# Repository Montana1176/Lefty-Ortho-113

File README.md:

# Lefty-Ortho-113
113 Key Ortholinear Keyboard with Left Num Pad

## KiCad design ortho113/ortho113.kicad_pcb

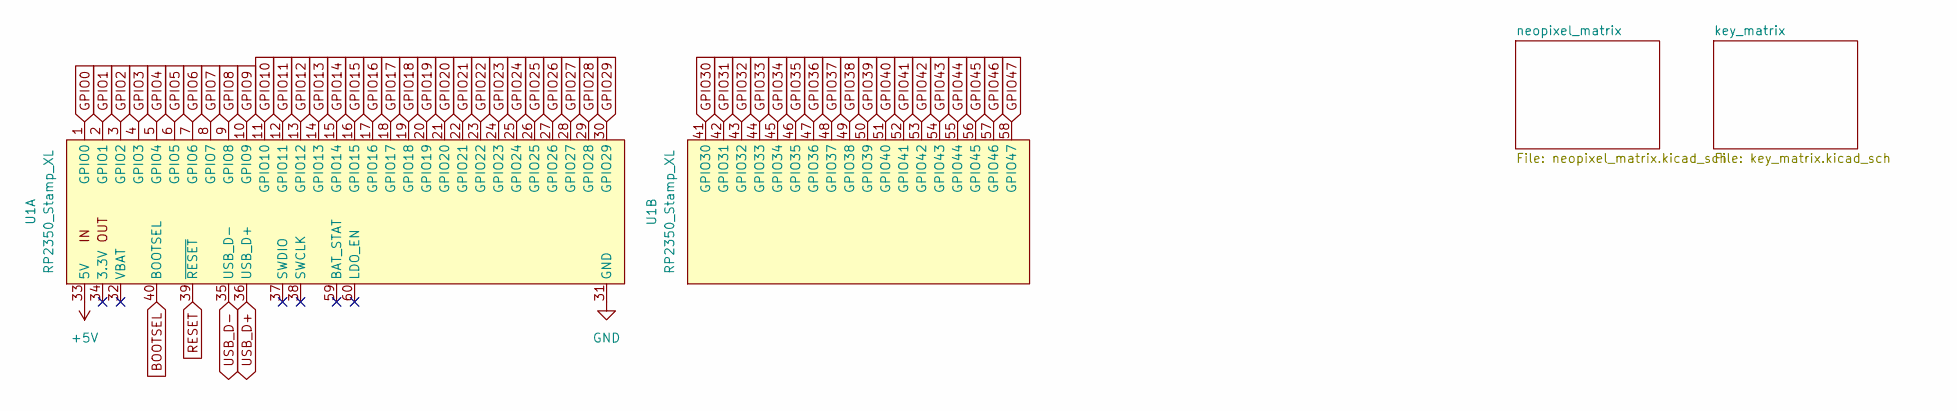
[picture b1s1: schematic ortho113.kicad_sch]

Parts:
U1: RP2350_Stamp_XL; RP2xxx_Stamp_XL_THT

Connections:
+5V: U1.33 (5V); also elsewhere on the board
BOOTSEL: U1.40 (BOOTSEL)
GND: U1.31 (GND); also elsewhere on the board
GPIO0: U1.1 (GPIO0)
GPIO1: U1.2 (GPIO1); also elsewhere on the board
GPIO2: U1.3 (GPIO2)
GPIO3: U1.4 (GPIO3)
GPIO4: U1.5 (GPIO4)
GPIO5: U1.6 (GPIO5)
GPIO6: U1.7 (GPIO6)
GPIO7: U1.8 (GPIO7)
GPIO8: U1.9 (GPIO8)
GPIO9: U1.10 (GPIO9)
GPIO10: U1.11 (GPIO10)
GPIO11: U1.12 (GPIO11)
GPIO12: U1.13 (GPIO12)
GPIO13: U1.14 (GPIO13)
GPIO14: U1.15 (GPIO14)
GPIO15: U1.16 (GPIO15)
GPIO16: U1.17 (GPIO16)
GPIO17: U1.18 (GPIO17)
GPIO18: U1.19 (GPIO18)
GPIO19: U1.20 (GPIO19)
GPIO20: U1.21 (GPIO20)
GPIO21: U1.22 (GPIO21)
GPIO22: U1.23 (GPIO22)
GPIO23: U1.24 (GPIO23)
GPIO24: U1.25 (GPIO24)
GPIO25: U1.26 (GPIO25)
GPIO26: U1.27 (GPIO26)
GPIO27: U1.28 (GPIO27)
GPIO28: U1.29 (GPIO28)
GPIO29: U1.30 (GPIO29)
GPIO30: U1.41 (GPIO30)
GPIO31: U1.42 (GPIO31)
GPIO32: U1.43 (GPIO32)
GPIO33: U1.44 (GPIO33)
GPIO34: U1.45 (GPIO34)
GPIO35: U1.46 (GPIO35)
GPIO36: U1.47 (GPIO36)
GPIO37: U1.48 (GPIO37)
GPIO38: U1.49 (GPIO38)
GPIO39: U1.50 (GPIO39)
GPIO40: U1.51 (GPIO40)
GPIO41: U1.52 (GPIO41)
GPIO42: U1.53 (GPIO42)
GPIO43: U1.54 (GPIO43)
GPIO44: U1.55 (GPIO44)
GPIO45: U1.56 (GPIO45)
GPIO46: U1.57 (GPIO46)
GPIO47: U1.58 (GPIO47)
RESET: U1.39 (~RESET)
USB_D+: U1.36 (USB_D+)
USB_D-: U1.35 (USB_D-)

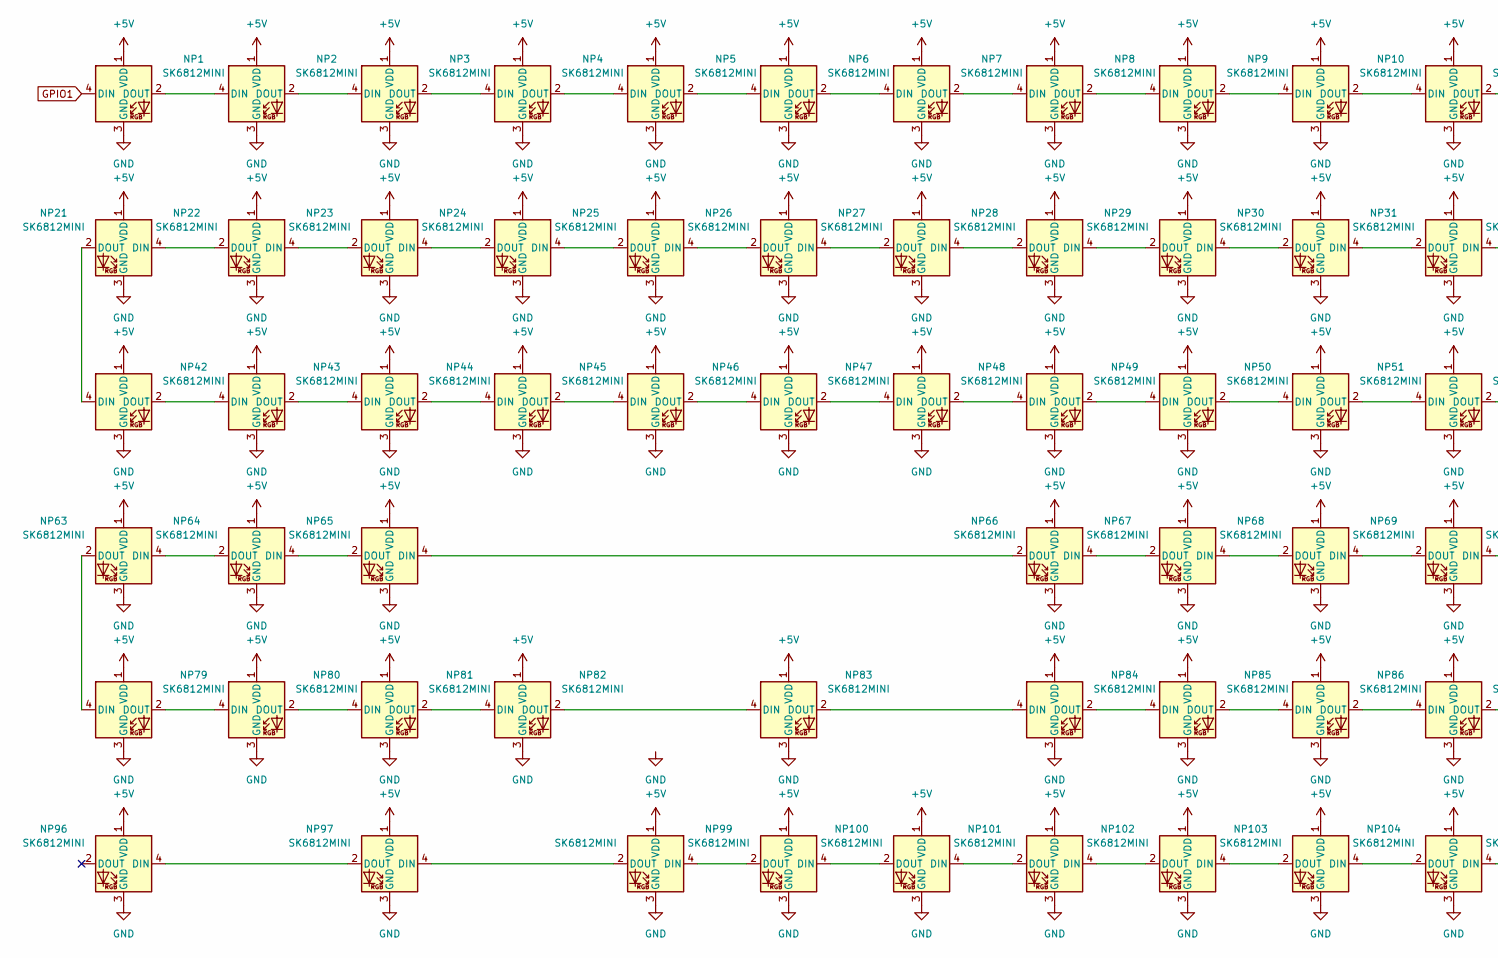
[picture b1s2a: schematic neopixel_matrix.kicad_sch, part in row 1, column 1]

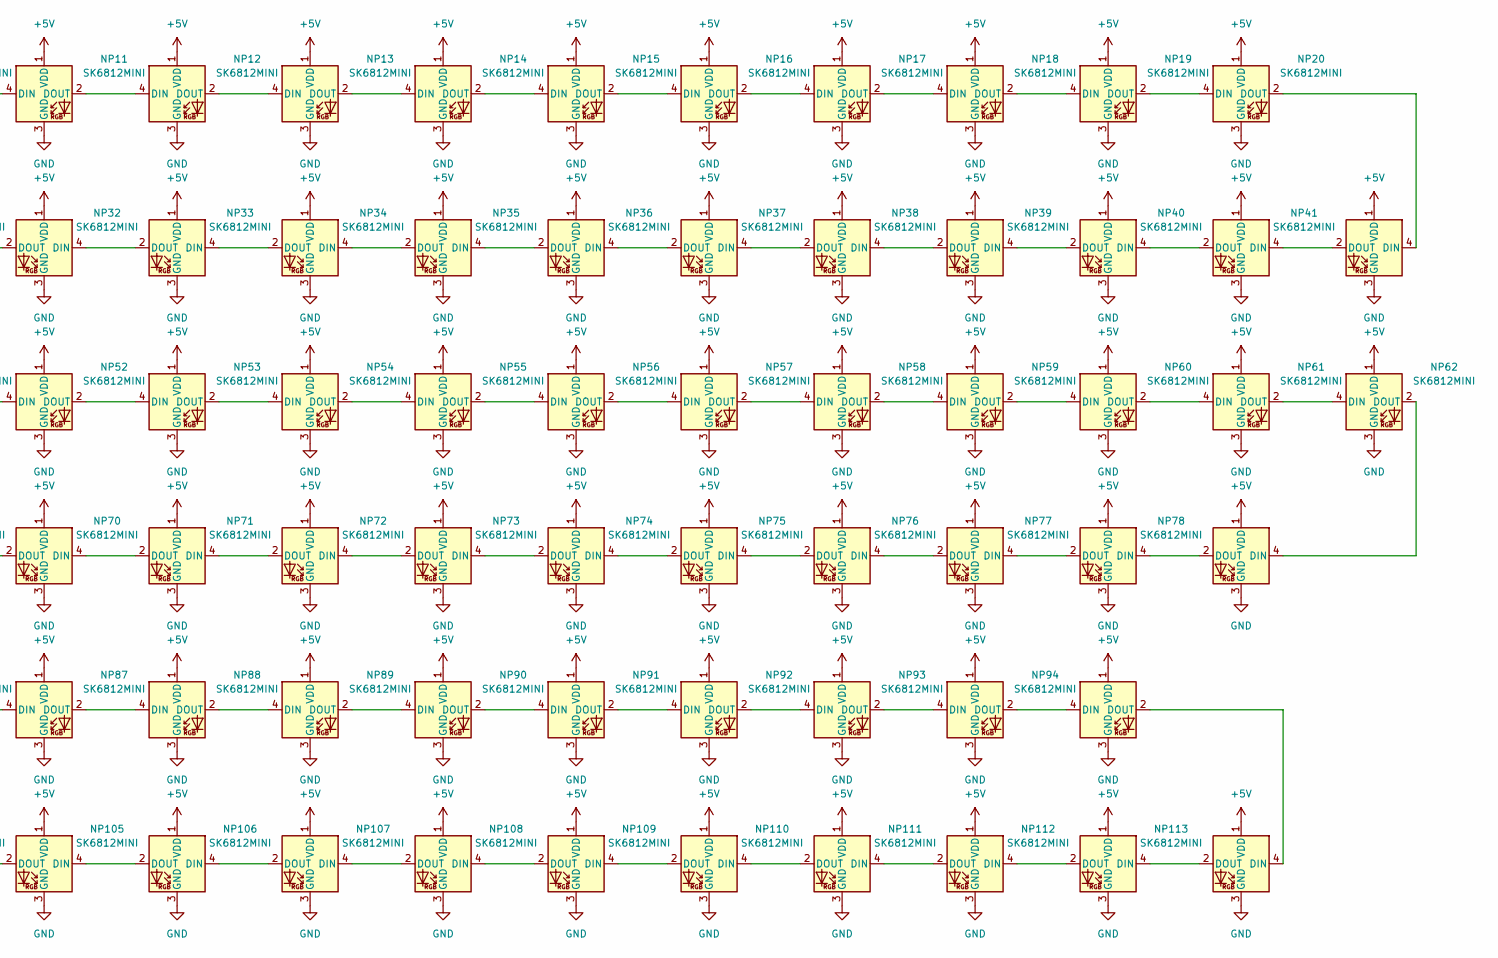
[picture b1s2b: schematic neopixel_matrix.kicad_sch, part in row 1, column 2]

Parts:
NP1, NP2, NP3, NP4, NP5, NP6, NP7, NP8, NP9, NP10, NP11, NP12, NP13, NP14, NP15, NP16, NP17, NP18, NP19, NP20, NP21, NP22, NP23, NP24, NP25, NP26, NP27, NP28, NP29, NP30, NP31, NP32, NP33, NP34, NP35, NP36, NP37, NP38, NP39, NP40, NP41, NP42, NP43, NP44, NP45, NP46, NP47, NP48, NP49, NP50, NP51, NP52, NP53, NP54, NP55, NP56, NP57, NP58, NP59, NP60, NP61, NP62, NP63, NP64, NP65, NP66, NP67, NP68, NP69, NP70, NP71, NP72, NP73, NP74, NP75, NP76, NP77, NP78, NP79, NP80, NP81, NP82, NP83, NP84, NP85, NP86, NP87, NP88, NP89, NP90, NP91, NP92, NP93, NP94, NP95, NP96, NP97, NP98, NP99, NP100, NP101, NP102, NP103, NP104, NP105, NP106, NP107, NP109, NP110, NP111, NP112, NP113: SK6812MINI; LED_SK6812MINI_PLCC4_3.5x3.5mm_P1.75mm
NP108: SK6812MINI; LED_SK6812MINI_E

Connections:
+5V: NP1.1 (VDD), NP2.1 (VDD), NP3.1 (VDD), NP4.1 (VDD), NP5.1 (VDD), NP6.1 (VDD), NP7.1 (VDD), NP8.1 (VDD), NP9.1 (VDD), NP10.1 (VDD), NP11.1 (VDD), NP12.1 (VDD), NP13.1 (VDD), NP14.1 (VDD), NP15.1 (VDD), NP16.1 (VDD), NP17.1 (VDD), NP18.1 (VDD), NP19.1 (VDD), NP20.1 (VDD), NP21.1 (VDD), NP22.1 (VDD), NP23.1 (VDD), NP24.1 (VDD), NP25.1 (VDD), NP26.1 (VDD), NP27.1 (VDD), NP28.1 (VDD), NP29.1 (VDD), NP30.1 (VDD), NP31.1 (VDD), NP32.1 (VDD), NP33.1 (VDD), NP34.1 (VDD), NP35.1 (VDD), NP36.1 (VDD), NP37.1 (VDD), NP38.1 (VDD), NP39.1 (VDD), NP40.1 (VDD), NP41.1 (VDD), NP42.1 (VDD), NP43.1 (VDD), NP44.1 (VDD), NP45.1 (VDD), NP46.1 (VDD), NP47.1 (VDD), NP48.1 (VDD), NP49.1 (VDD), NP50.1 (VDD), NP51.1 (VDD), NP52.1 (VDD), NP53.1 (VDD), NP54.1 (VDD), NP55.1 (VDD), NP56.1 (VDD), NP57.1 (VDD), NP58.1 (VDD), NP59.1 (VDD), NP60.1 (VDD), NP61.1 (VDD), NP62.1 (VDD), NP63.1 (VDD), NP64.1 (VDD), NP65.1 (VDD), NP66.1 (VDD), NP67.1 (VDD), NP68.1 (VDD), NP69.1 (VDD), NP70.1 (VDD), NP71.1 (VDD), NP72.1 (VDD), NP73.1 (VDD), NP74.1 (VDD), NP75.1 (VDD), NP76.1 (VDD), NP77.1 (VDD), NP78.1 (VDD), NP79.1 (VDD), NP80.1 (VDD), NP81.1 (VDD), NP82.1 (VDD), NP83.1 (VDD), NP84.1 (VDD), NP85.1 (VDD), NP86.1 (VDD), NP87.1 (VDD), NP88.1 (VDD), NP89.1 (VDD), NP90.1 (VDD), NP91.1 (VDD), NP92.1 (VDD), NP93.1 (VDD), NP94.1 (VDD), NP95.1 (VDD), NP96.1 (VDD), NP97.1 (VDD), NP98.1 (VDD), NP99.1 (VDD), NP100.1 (VDD), NP101.1 (VDD), NP102.1 (VDD), NP103.1 (VDD), NP104.1 (VDD), NP105.1 (VDD), NP106.1 (VDD), NP107.1 (VDD), NP108.1 (VDD), NP109.1 (VDD), NP110.1 (VDD), NP111.1 (VDD), NP112.1 (VDD), NP113.1 (VDD); also elsewhere on the board
GND: NP1.3 (GND), NP2.3 (GND), NP3.3 (GND), NP4.3 (GND), NP5.3 (GND), NP6.3 (GND), NP7.3 (GND), NP8.3 (GND), NP9.3 (GND), NP10.3 (GND), NP11.3 (GND), NP12.3 (GND), NP13.3 (GND), NP14.3 (GND), NP15.3 (GND), NP16.3 (GND), NP17.3 (GND), NP18.3 (GND), NP19.3 (GND), NP20.3 (GND), NP21.3 (GND), NP22.3 (GND), NP23.3 (GND), NP24.3 (GND), NP25.3 (GND), NP26.3 (GND), NP27.3 (GND), NP28.3 (GND), NP29.3 (GND), NP30.3 (GND), NP31.3 (GND), NP32.3 (GND), NP33.3 (GND), NP34.3 (GND), NP35.3 (GND), NP36.3 (GND), NP37.3 (GND), NP38.3 (GND), NP39.3 (GND), NP40.3 (GND), NP41.3 (GND), NP42.3 (GND), NP43.3 (GND), NP44.3 (GND), NP45.3 (GND), NP46.3 (GND), NP47.3 (GND), NP48.3 (GND), NP49.3 (GND), NP50.3 (GND), NP51.3 (GND), NP52.3 (GND), NP53.3 (GND), NP54.3 (GND), NP55.3 (GND), NP56.3 (GND), NP57.3 (GND), NP58.3 (GND), NP59.3 (GND), NP60.3 (GND), NP61.3 (GND), NP62.3 (GND), NP63.3 (GND), NP64.3 (GND), NP65.3 (GND), NP66.3 (GND), NP67.3 (GND), NP68.3 (GND), NP69.3 (GND), NP70.3 (GND), NP71.3 (GND), NP72.3 (GND), NP73.3 (GND), NP74.3 (GND), NP75.3 (GND), NP76.3 (GND), NP77.3 (GND), NP78.3 (GND), NP79.3 (GND), NP80.3 (GND), NP81.3 (GND), NP82.3 (GND), NP83.3 (GND), NP84.3 (GND), NP85.3 (GND), NP86.3 (GND), NP87.3 (GND), NP88.3 (GND), NP89.3 (GND), NP90.3 (GND), NP91.3 (GND), NP92.3 (GND), NP93.3 (GND), NP94.3 (GND), NP95.3 (GND), NP96.3 (GND), NP97.3 (GND), NP98.3 (GND), NP99.3 (GND), NP100.3 (GND), NP101.3 (GND), NP102.3 (GND), NP103.3 (GND), NP104.3 (GND), NP105.3 (GND), NP106.3 (GND), NP107.3 (GND), NP108.3 (GND), NP109.3 (GND), NP110.3 (GND), NP111.3 (GND), NP112.3 (GND), NP113.3 (GND); also elsewhere on the board
GPIO1: NP1.4 (DIN); also elsewhere on the board
unnamed: NP1.2 (DOUT), NP2.4 (DIN)
unnamed: NP2.2 (DOUT), NP3.4 (DIN)
unnamed: NP3.2 (DOUT), NP4.4 (DIN)
unnamed: NP4.2 (DOUT), NP5.4 (DIN)
unnamed: NP5.2 (DOUT), NP6.4 (DIN)
unnamed: NP6.2 (DOUT), NP7.4 (DIN)
unnamed: NP7.2 (DOUT), NP8.4 (DIN)
unnamed: NP8.2 (DOUT), NP9.4 (DIN)
unnamed: NP9.2 (DOUT), NP10.4 (DIN)
unnamed: NP10.2 (DOUT), NP11.4 (DIN)
unnamed: NP11.2 (DOUT), NP12.4 (DIN)
unnamed: NP12.2 (DOUT), NP13.4 (DIN)
unnamed: NP13.2 (DOUT), NP14.4 (DIN)
unnamed: NP14.2 (DOUT), NP15.4 (DIN)
unnamed: NP15.2 (DOUT), NP16.4 (DIN)
unnamed: NP16.2 (DOUT), NP17.4 (DIN)
unnamed: NP17.2 (DOUT), NP18.4 (DIN)
unnamed: NP18.2 (DOUT), NP19.4 (DIN)
unnamed: NP19.2 (DOUT), NP20.4 (DIN)
unnamed: NP20.2 (DOUT), NP41.4 (DIN)
unnamed: NP21.4 (DIN), NP22.2 (DOUT)
unnamed: NP21.2 (DOUT), NP42.4 (DIN)
unnamed: NP22.4 (DIN), NP23.2 (DOUT)
unnamed: NP23.4 (DIN), NP24.2 (DOUT)
unnamed: NP24.4 (DIN), NP25.2 (DOUT)
unnamed: NP25.4 (DIN), NP26.2 (DOUT)
unnamed: NP26.4 (DIN), NP27.2 (DOUT)
unnamed: NP27.4 (DIN), NP28.2 (DOUT)
unnamed: NP28.4 (DIN), NP29.2 (DOUT)
unnamed: NP29.4 (DIN), NP30.2 (DOUT)
unnamed: NP30.4 (DIN), NP31.2 (DOUT)
unnamed: NP31.4 (DIN), NP32.2 (DOUT)
unnamed: NP32.4 (DIN), NP33.2 (DOUT)
unnamed: NP33.4 (DIN), NP34.2 (DOUT)
unnamed: NP34.4 (DIN), NP35.2 (DOUT)
unnamed: NP35.4 (DIN), NP36.2 (DOUT)
unnamed: NP36.4 (DIN), NP37.2 (DOUT)
unnamed: NP37.4 (DIN), NP38.2 (DOUT)
unnamed: NP38.4 (DIN), NP39.2 (DOUT)
unnamed: NP39.4 (DIN), NP40.2 (DOUT)
unnamed: NP40.4 (DIN), NP41.2 (DOUT)
unnamed: NP42.2 (DOUT), NP43.4 (DIN)
unnamed: NP43.2 (DOUT), NP44.4 (DIN)
unnamed: NP44.2 (DOUT), NP45.4 (DIN)
unnamed: NP45.2 (DOUT), NP46.4 (DIN)
unnamed: NP46.2 (DOUT), NP47.4 (DIN)
unnamed: NP47.2 (DOUT), NP48.4 (DIN)
unnamed: NP48.2 (DOUT), NP49.4 (DIN)
unnamed: NP49.2 (DOUT), NP50.4 (DIN)
unnamed: NP50.2 (DOUT), NP51.4 (DIN)
unnamed: NP51.2 (DOUT), NP52.4 (DIN)
unnamed: NP52.2 (DOUT), NP53.4 (DIN)
unnamed: NP53.2 (DOUT), NP54.4 (DIN)
unnamed: NP54.2 (DOUT), NP55.4 (DIN)
unnamed: NP55.2 (DOUT), NP56.4 (DIN)
unnamed: NP56.2 (DOUT), NP57.4 (DIN)
unnamed: NP57.2 (DOUT), NP58.4 (DIN)
unnamed: NP58.2 (DOUT), NP59.4 (DIN)
unnamed: NP59.2 (DOUT), NP60.4 (DIN)
unnamed: NP60.2 (DOUT), NP61.4 (DIN)
unnamed: NP61.2 (DOUT), NP62.4 (DIN)
unnamed: NP62.2 (DOUT), NP78.4 (DIN)
unnamed: NP63.4 (DIN), NP64.2 (DOUT)
unnamed: NP63.2 (DOUT), NP79.4 (DIN)
unnamed: NP64.4 (DIN), NP65.2 (DOUT)
unnamed: NP65.4 (DIN), NP66.2 (DOUT)
unnamed: NP66.4 (DIN), NP67.2 (DOUT)
unnamed: NP67.4 (DIN), NP68.2 (DOUT)
unnamed: NP68.4 (DIN), NP69.2 (DOUT)
unnamed: NP69.4 (DIN), NP70.2 (DOUT)
unnamed: NP70.4 (DIN), NP71.2 (DOUT)
unnamed: NP71.4 (DIN), NP72.2 (DOUT)
unnamed: NP72.4 (DIN), NP73.2 (DOUT)
unnamed: NP73.4 (DIN), NP74.2 (DOUT)
unnamed: NP74.4 (DIN), NP75.2 (DOUT)
unnamed: NP75.4 (DIN), NP76.2 (DOUT)
unnamed: NP76.4 (DIN), NP77.2 (DOUT)
unnamed: NP77.4 (DIN), NP78.2 (DOUT)
unnamed: NP79.2 (DOUT), NP80.4 (DIN)
unnamed: NP80.2 (DOUT), NP81.4 (DIN)
unnamed: NP81.2 (DOUT), NP82.4 (DIN)
unnamed: NP82.2 (DOUT), NP83.4 (DIN)
unnamed: NP83.2 (DOUT), NP84.4 (DIN)
unnamed: NP84.2 (DOUT), NP85.4 (DIN)
unnamed: NP85.2 (DOUT), NP86.4 (DIN)
unnamed: NP86.2 (DOUT), NP87.4 (DIN)
unnamed: NP87.2 (DOUT), NP88.4 (DIN)
unnamed: NP88.2 (DOUT), NP89.4 (DIN)
unnamed: NP89.2 (DOUT), NP90.4 (DIN)
unnamed: NP90.2 (DOUT), NP91.4 (DIN)
unnamed: NP91.2 (DOUT), NP92.4 (DIN)
unnamed: NP92.2 (DOUT), NP93.4 (DIN)
unnamed: NP93.2 (DOUT), NP94.4 (DIN)
unnamed: NP94.2 (DOUT), NP95.4 (DIN)
unnamed: NP96.4 (DIN), NP97.2 (DOUT)
unnamed: NP97.4 (DIN), NP98.2 (DOUT)
unnamed: NP98.4 (DIN), NP99.2 (DOUT)
unnamed: NP100.4 (DIN), NP101.2 (DOUT)
unnamed: NP99.4 (DIN), NP100.2 (DOUT)
unnamed: NP101.4 (DIN), NP102.2 (DOUT)
unnamed: NP102.4 (DIN), NP103.2 (DOUT)
unnamed: NP103.4 (DIN), NP104.2 (DOUT)
unnamed: NP104.4 (DIN), NP105.2 (DOUT)
unnamed: NP105.4 (DIN), NP106.2 (DOUT)
unnamed: NP106.4 (DIN), NP107.2 (DOUT)
unnamed: NP107.4 (DIN), NP108.2 (DOUT)
unnamed: NP108.4 (DIN), NP109.2 (DOUT)
unnamed: NP109.4 (DIN), NP110.2 (DOUT)
unnamed: NP110.4 (DIN), NP111.2 (DOUT)
unnamed: NP111.4 (DIN), NP112.2 (DOUT)
unnamed: NP112.4 (DIN), NP113.2 (DOUT)
unnamed: NP95.2 (DOUT), NP113.4 (DIN)

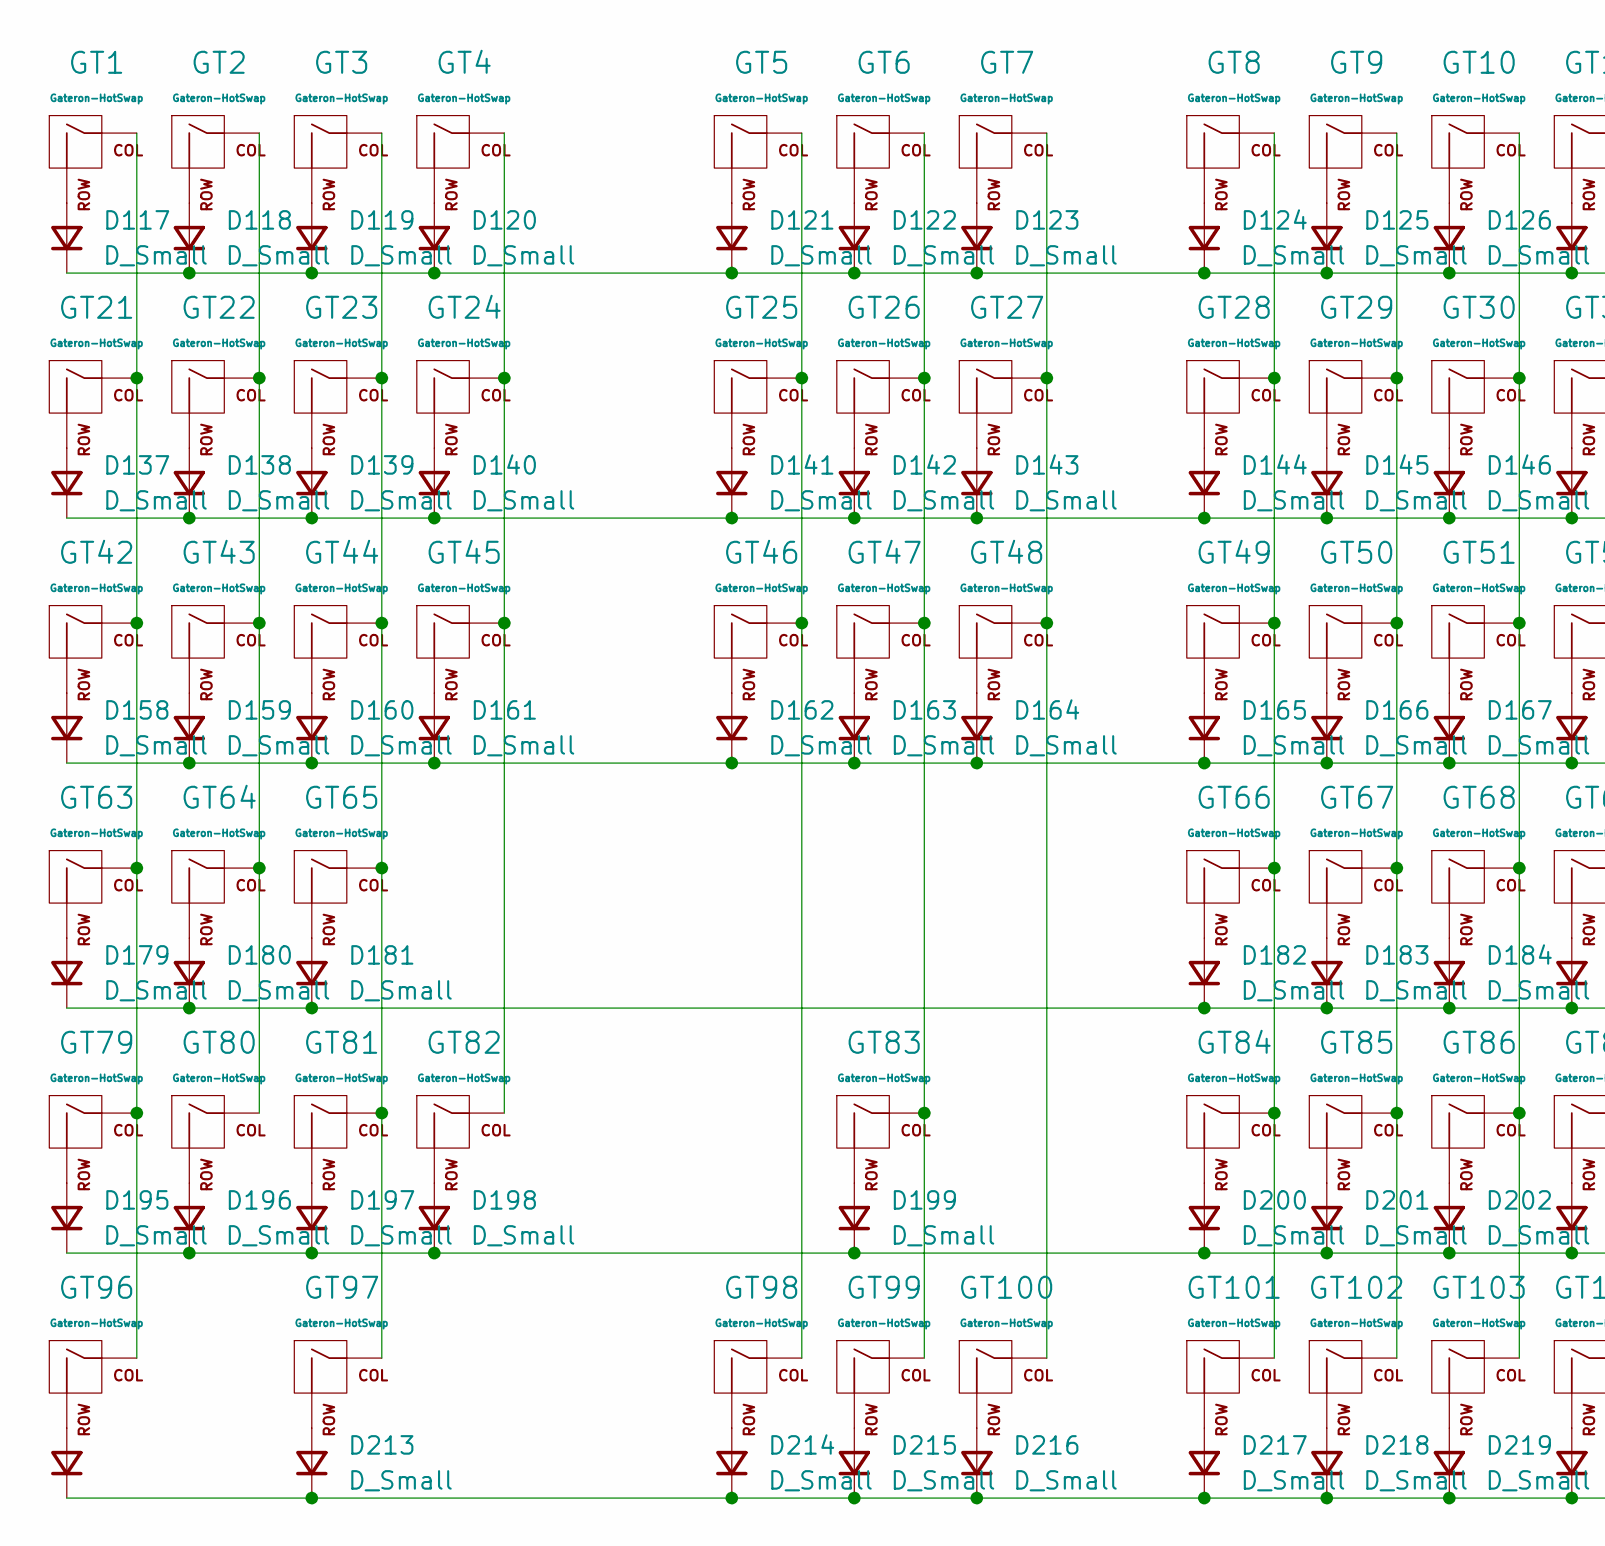
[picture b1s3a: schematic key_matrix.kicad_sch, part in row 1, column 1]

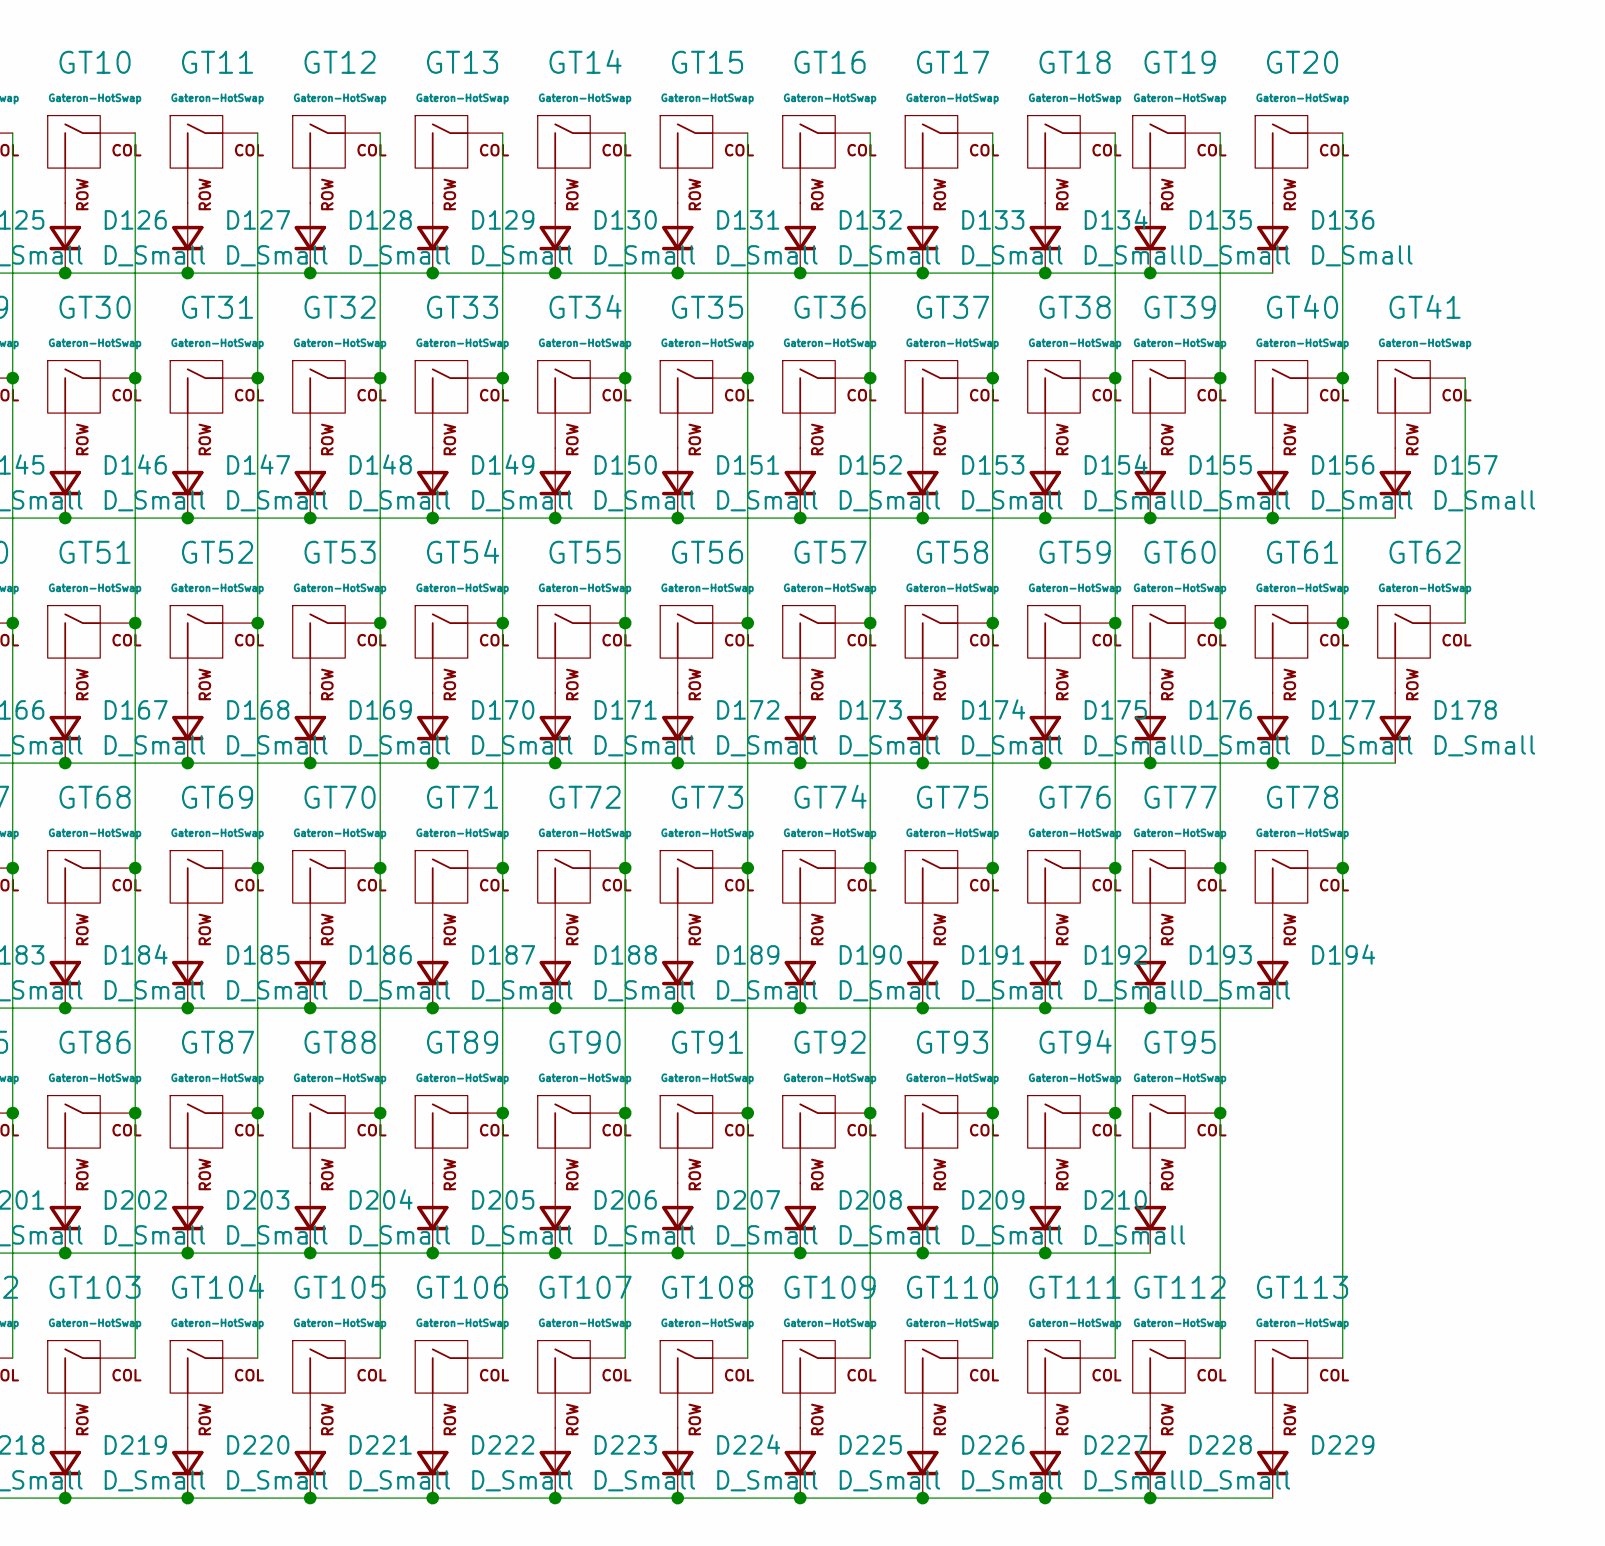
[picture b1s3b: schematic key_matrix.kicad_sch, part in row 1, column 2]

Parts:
D117, D118, D119, D120, D121, D122, D123, D124, D125, D126, D127, D128, D129, D130, D131, D132, D133, D134, D135, D136, D137, D138, D139, D140, D141, D142, D143, D144, D145, D146, D147, D148, D149, D150, D151, D152, D153, D154, D155, D156, D157, D158, D159, D160, D161, D162, D163, D164, D165, D166, D167, D168, D169, D170, D171, D172, D173, D174, D175, D176, D177, D178, D179, D180, D181, D182, D183, D184, D185, D186, D187, D188, D189, D190, D191, D192, D193, D194, D195, D196, D197, D198, D199, D200, D201, D202, D203, D204, D205, D206, D207, D208, D209, D210, D211, D212, D213, D214, D215, D216, D217, D218, D219, D220, D221, D222, D223, D224, D225, D226, D227, D228, D229: D_Small; D_SOD-123-Pretty
GT1, GT2, GT3, GT4, GT5, GT6, GT7, GT8, GT9, GT10, GT11, GT12, GT13, GT14, GT15, GT16, GT17, GT18, GT19, GT20, GT21, GT22, GT23, GT24, GT25, GT26, GT27, GT28, GT29, GT30, GT31, GT32, GT33, GT34, GT35, GT36, GT37, GT38, GT39, GT40, GT41, GT42, GT43, GT44, GT45, GT46, GT47, GT48, GT49, GT50, GT51, GT52, GT53, GT54, GT55, GT56, GT57, GT58, GT59, GT60, GT61, GT62, GT63, GT64, GT65, GT66, GT67, GT68, GT69, GT70, GT71, GT72, GT73, GT74, GT75, GT76, GT77, GT78, GT79, GT80, GT81, GT82, GT83, GT84, GT85, GT86, GT87, GT88, GT89, GT90, GT91, GT92, GT93, GT94, GT95, GT96, GT97, GT98, GT99, GT100, GT101, GT102, GT103, GT104, GT105, GT106, GT107, GT108, GT109, GT110, GT111, GT112, GT113: Gateron-HotSwap; SW_Gateron_LowProfile_HotSwap_PTH

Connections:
unnamed: D117.2 (A), GT1.2 (ROW)
unnamed: D117.1 (K), D118.1 (K), D119.1 (K), D120.1 (K), D121.1 (K), D122.1 (K), D123.1 (K), D124.1 (K), D125.1 (K), D126.1 (K), D127.1 (K), D128.1 (K), D129.1 (K), D130.1 (K), D131.1 (K), D132.1 (K), D133.1 (K), D134.1 (K), D135.1 (K), D136.1 (K)
unnamed: D118.2 (A), GT2.2 (ROW)
unnamed: D119.2 (A), GT3.2 (ROW)
unnamed: D120.2 (A), GT4.2 (ROW)
unnamed: D121.2 (A), GT5.2 (ROW)
unnamed: D122.2 (A), GT6.2 (ROW)
unnamed: D123.2 (A), GT7.2 (ROW)
unnamed: D124.2 (A), GT8.2 (ROW)
unnamed: D125.2 (A), GT9.2 (ROW)
unnamed: D126.2 (A), GT10.2 (ROW)
unnamed: D127.2 (A), GT11.2 (ROW)
unnamed: D128.2 (A), GT12.2 (ROW)
unnamed: D129.2 (A), GT13.2 (ROW)
unnamed: D130.2 (A), GT14.2 (ROW)
unnamed: D131.2 (A), GT15.2 (ROW)
unnamed: D132.2 (A), GT16.2 (ROW)
unnamed: D133.2 (A), GT17.2 (ROW)
unnamed: D134.2 (A), GT18.2 (ROW)
unnamed: D135.2 (A), GT19.2 (ROW)
unnamed: D136.2 (A), GT20.2 (ROW)
unnamed: D137.2 (A), GT21.2 (ROW)
unnamed: D137.1 (K), D138.1 (K), D139.1 (K), D140.1 (K), D141.1 (K), D142.1 (K), D143.1 (K), D144.1 (K), D145.1 (K), D146.1 (K), D147.1 (K), D148.1 (K), D149.1 (K), D150.1 (K), D151.1 (K), D152.1 (K), D153.1 (K), D154.1 (K), D155.1 (K), D156.1 (K), D157.1 (K)
unnamed: D138.2 (A), GT22.2 (ROW)
unnamed: D139.2 (A), GT23.2 (ROW)
unnamed: D140.2 (A), GT24.2 (ROW)
unnamed: D141.2 (A), GT25.2 (ROW)
unnamed: D142.2 (A), GT26.2 (ROW)
unnamed: D143.2 (A), GT27.2 (ROW)
unnamed: D144.2 (A), GT28.2 (ROW)
unnamed: D145.2 (A), GT29.2 (ROW)
unnamed: D146.2 (A), GT30.2 (ROW)
unnamed: D147.2 (A), GT31.2 (ROW)
unnamed: D148.2 (A), GT32.2 (ROW)
unnamed: D149.2 (A), GT33.2 (ROW)
unnamed: D150.2 (A), GT34.2 (ROW)
unnamed: D151.2 (A), GT35.2 (ROW)
unnamed: D152.2 (A), GT36.2 (ROW)
unnamed: D153.2 (A), GT37.2 (ROW)
unnamed: D154.2 (A), GT38.2 (ROW)
unnamed: D155.2 (A), GT39.2 (ROW)
unnamed: D156.2 (A), GT40.2 (ROW)
unnamed: D157.2 (A), GT41.2 (ROW)
unnamed: D158.2 (A), GT42.2 (ROW)
unnamed: D158.1 (K), D159.1 (K), D160.1 (K), D161.1 (K), D162.1 (K), D163.1 (K), D164.1 (K), D165.1 (K), D166.1 (K), D167.1 (K), D168.1 (K), D169.1 (K), D170.1 (K), D171.1 (K), D172.1 (K), D173.1 (K), D174.1 (K), D175.1 (K), D176.1 (K), D177.1 (K), D178.1 (K)
unnamed: D159.2 (A), GT43.2 (ROW)
unnamed: D160.2 (A), GT44.2 (ROW)
unnamed: D161.2 (A), GT45.2 (ROW)
unnamed: D162.2 (A), GT46.2 (ROW)
unnamed: D163.2 (A), GT47.2 (ROW)
unnamed: D164.2 (A), GT48.2 (ROW)
unnamed: D165.2 (A), GT49.2 (ROW)
unnamed: D166.2 (A), GT50.2 (ROW)
unnamed: D167.2 (A), GT51.2 (ROW)
unnamed: D168.2 (A), GT52.2 (ROW)
unnamed: D169.2 (A), GT53.2 (ROW)
unnamed: D170.2 (A), GT54.2 (ROW)
unnamed: D171.2 (A), GT55.2 (ROW)
unnamed: D172.2 (A), GT56.2 (ROW)
unnamed: D173.2 (A), GT57.2 (ROW)
unnamed: D174.2 (A), GT58.2 (ROW)
unnamed: D175.2 (A), GT59.2 (ROW)
unnamed: D176.2 (A), GT60.2 (ROW)
unnamed: D177.2 (A), GT61.2 (ROW)
unnamed: D178.2 (A), GT62.2 (ROW)
unnamed: D179.2 (A), GT63.2 (ROW)
unnamed: D179.1 (K), D180.1 (K), D181.1 (K), D182.1 (K), D183.1 (K), D184.1 (K), D185.1 (K), D186.1 (K), D187.1 (K), D188.1 (K), D189.1 (K), D190.1 (K), D191.1 (K), D192.1 (K), D193.1 (K), D194.1 (K)
unnamed: D180.2 (A), GT64.2 (ROW)
unnamed: D181.2 (A), GT65.2 (ROW)
unnamed: D182.2 (A), GT66.2 (ROW)
unnamed: D183.2 (A), GT67.2 (ROW)
unnamed: D184.2 (A), GT68.2 (ROW)
unnamed: D185.2 (A), GT69.2 (ROW)
unnamed: D186.2 (A), GT70.2 (ROW)
unnamed: D187.2 (A), GT71.2 (ROW)
unnamed: D188.2 (A), GT72.2 (ROW)
unnamed: D189.2 (A), GT73.2 (ROW)
unnamed: D190.2 (A), GT74.2 (ROW)
unnamed: D191.2 (A), GT75.2 (ROW)
unnamed: D192.2 (A), GT76.2 (ROW)
unnamed: D193.2 (A), GT77.2 (ROW)
unnamed: D194.2 (A), GT78.2 (ROW)
unnamed: D195.2 (A), GT79.2 (ROW)
unnamed: D195.1 (K), D196.1 (K), D197.1 (K), D198.1 (K), D199.1 (K), D200.1 (K), D201.1 (K), D202.1 (K), D203.1 (K), D204.1 (K), D205.1 (K), D206.1 (K), D207.1 (K), D208.1 (K), D209.1 (K), D210.1 (K), D211.1 (K)
unnamed: D196.2 (A), GT80.2 (ROW)
unnamed: D197.2 (A), GT81.2 (ROW)
unnamed: D198.2 (A), GT82.2 (ROW)
unnamed: D199.2 (A), GT83.2 (ROW)
unnamed: D200.2 (A), GT84.2 (ROW)
unnamed: D201.2 (A), GT85.2 (ROW)
unnamed: D202.2 (A), GT86.2 (ROW)
unnamed: D203.2 (A), GT87.2 (ROW)
unnamed: D204.2 (A), GT88.2 (ROW)
unnamed: D205.2 (A), GT89.2 (ROW)
unnamed: D206.2 (A), GT90.2 (ROW)
unnamed: D207.2 (A), GT91.2 (ROW)
unnamed: D208.2 (A), GT92.2 (ROW)
unnamed: D209.2 (A), GT93.2 (ROW)
unnamed: D210.2 (A), GT94.2 (ROW)
unnamed: D211.2 (A), GT95.2 (ROW)
unnamed: D212.2 (A), GT96.2 (ROW)
unnamed: D212.1 (K), D213.1 (K), D214.1 (K), D215.1 (K), D216.1 (K), D217.1 (K), D218.1 (K), D219.1 (K), D220.1 (K), D221.1 (K), D222.1 (K), D223.1 (K), D224.1 (K), D225.1 (K), D226.1 (K), D227.1 (K), D228.1 (K), D229.1 (K)
unnamed: D213.2 (A), GT97.2 (ROW)
unnamed: D214.2 (A), GT98.2 (ROW)
unnamed: D215.2 (A), GT99.2 (ROW)
unnamed: D216.2 (A), GT100.2 (ROW)
unnamed: D217.2 (A), GT101.2 (ROW)
unnamed: D218.2 (A), GT102.2 (ROW)
unnamed: D219.2 (A), GT103.2 (ROW)
unnamed: D220.2 (A), GT104.2 (ROW)
unnamed: D221.2 (A), GT105.2 (ROW)
unnamed: D222.2 (A), GT106.2 (ROW)
unnamed: D223.2 (A), GT107.2 (ROW)
unnamed: D224.2 (A), GT108.2 (ROW)
unnamed: D225.2 (A), GT109.2 (ROW)
unnamed: D226.2 (A), GT110.2 (ROW)
unnamed: D227.2 (A), GT111.2 (ROW)
unnamed: D228.2 (A), GT112.2 (ROW)
unnamed: D229.2 (A), GT113.2 (ROW)
unnamed: GT1.1 (COL), GT21.1 (COL), GT42.1 (COL), GT63.1 (COL), GT79.1 (COL), GT96.1 (COL)
unnamed: GT2.1 (COL), GT22.1 (COL), GT43.1 (COL), GT64.1 (COL), GT80.1 (COL)
unnamed: GT10.1 (COL), GT30.1 (COL), GT51.1 (COL), GT68.1 (COL), GT86.1 (COL), GT103.1 (COL)
unnamed: GT3.1 (COL), GT23.1 (COL), GT44.1 (COL), GT65.1 (COL), GT81.1 (COL), GT97.1 (COL)
unnamed: GT4.1 (COL), GT24.1 (COL), GT45.1 (COL), GT82.1 (COL)
unnamed: GT5.1 (COL), GT25.1 (COL), GT46.1 (COL), GT98.1 (COL)
unnamed: GT6.1 (COL), GT26.1 (COL), GT47.1 (COL), GT83.1 (COL), GT99.1 (COL)
unnamed: GT41.1 (COL), GT62.1 (COL)
unnamed: GT7.1 (COL), GT27.1 (COL), GT48.1 (COL), GT100.1 (COL)
unnamed: GT8.1 (COL), GT28.1 (COL), GT49.1 (COL), GT66.1 (COL), GT84.1 (COL), GT101.1 (COL)
unnamed: GT9.1 (COL), GT29.1 (COL), GT50.1 (COL), GT67.1 (COL), GT85.1 (COL), GT102.1 (COL)
unnamed: GT11.1 (COL), GT31.1 (COL), GT52.1 (COL), GT69.1 (COL), GT87.1 (COL), GT104.1 (COL)
unnamed: GT12.1 (COL), GT32.1 (COL), GT53.1 (COL), GT70.1 (COL), GT88.1 (COL), GT105.1 (COL)
unnamed: GT13.1 (COL), GT33.1 (COL), GT54.1 (COL), GT71.1 (COL), GT89.1 (COL), GT106.1 (COL)
unnamed: GT14.1 (COL), GT34.1 (COL), GT55.1 (COL), GT72.1 (COL), GT90.1 (COL), GT107.1 (COL)
unnamed: GT15.1 (COL), GT35.1 (COL), GT56.1 (COL), GT73.1 (COL), GT91.1 (COL), GT108.1 (COL)
unnamed: GT16.1 (COL), GT36.1 (COL), GT57.1 (COL), GT74.1 (COL), GT92.1 (COL), GT109.1 (COL)
unnamed: GT17.1 (COL), GT37.1 (COL), GT58.1 (COL), GT75.1 (COL), GT93.1 (COL), GT110.1 (COL)
unnamed: GT18.1 (COL), GT38.1 (COL), GT59.1 (COL), GT76.1 (COL), GT94.1 (COL), GT111.1 (COL)
unnamed: GT19.1 (COL), GT39.1 (COL), GT60.1 (COL), GT77.1 (COL), GT95.1 (COL), GT112.1 (COL)
unnamed: GT20.1 (COL), GT40.1 (COL), GT61.1 (COL), GT78.1 (COL), GT113.1 (COL)

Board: 2 copper layers, 340 parts (0 on the bottom side), 255 nets, no tracks yet.

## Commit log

2021-12-31 Add submodules
2021-12-31 Added footprint libraries
2022-01-03 started schematic
2024-06-22 update to kicad 8
2024-08-11 added target layout
    -added layout png and json
    -updated to kicad 8.0.4
2024-08-11 added ki-lime-pi-pico
    rp pico footprints for kicad
    https://github.com/recursivenomad/ki-lime-pi-pico
2024-08-12 updated png + added ergogen beginnings
2024-08-12 added stagger column variant & matrix drawing
2024-08-12 fixed stagger
2024-08-15 Added more key switch footprints
    https://github.com/siderakb/key-switches.pretty
2024-08-15 created custom gateron footprint
    custom gateron low profile hotswap footprint with SK6812MINI-E led socket
2024-08-25 made ergogen files
2024-08-25 added rp2xxx footprints
    https://github.com/solderparty/rp2xxx_stamp_footprints
2024-08-25 fixed ergogen files
    also restarted schematic with rp2350
2024-08-25 ergogen-erated layout pcbs for both varients
2024-08-25 ortho layout schematic
    made room for the controller
2024-08-25 fixed custom footprint & ran matrix traces
    - fixed issue with footprint not having neopixel cutout
    - fixed issue with neopixel pads being on top instead of bottom
2024-08-25 added type c footprints
    https://github.com/ai03-2725/Type-C.pretty
2024-08-26 rows & columns routed
    Todo: LEDs and USB
2024-08-27 fixed unlinked schematic and pcb files
2024-08-29 fixed submodule conflict & remove gitignore
    added pinout for oled display
    finished rev1 of pcb design
2024-08-29 fixed drc errors
2024-08-29 generated jlcpcb files
2024-08-29 Update README.md
    fixed readme to match repo name change
2024-09-11 continued pcb optimization/tweaks
2024-12-05 forgot to push changes to main
    don't remember what happened here
2024-12-08 update prod files, add versioning and makermark silkscreen
2024-12-08 forgot to save pcb w/ prior commit changes
